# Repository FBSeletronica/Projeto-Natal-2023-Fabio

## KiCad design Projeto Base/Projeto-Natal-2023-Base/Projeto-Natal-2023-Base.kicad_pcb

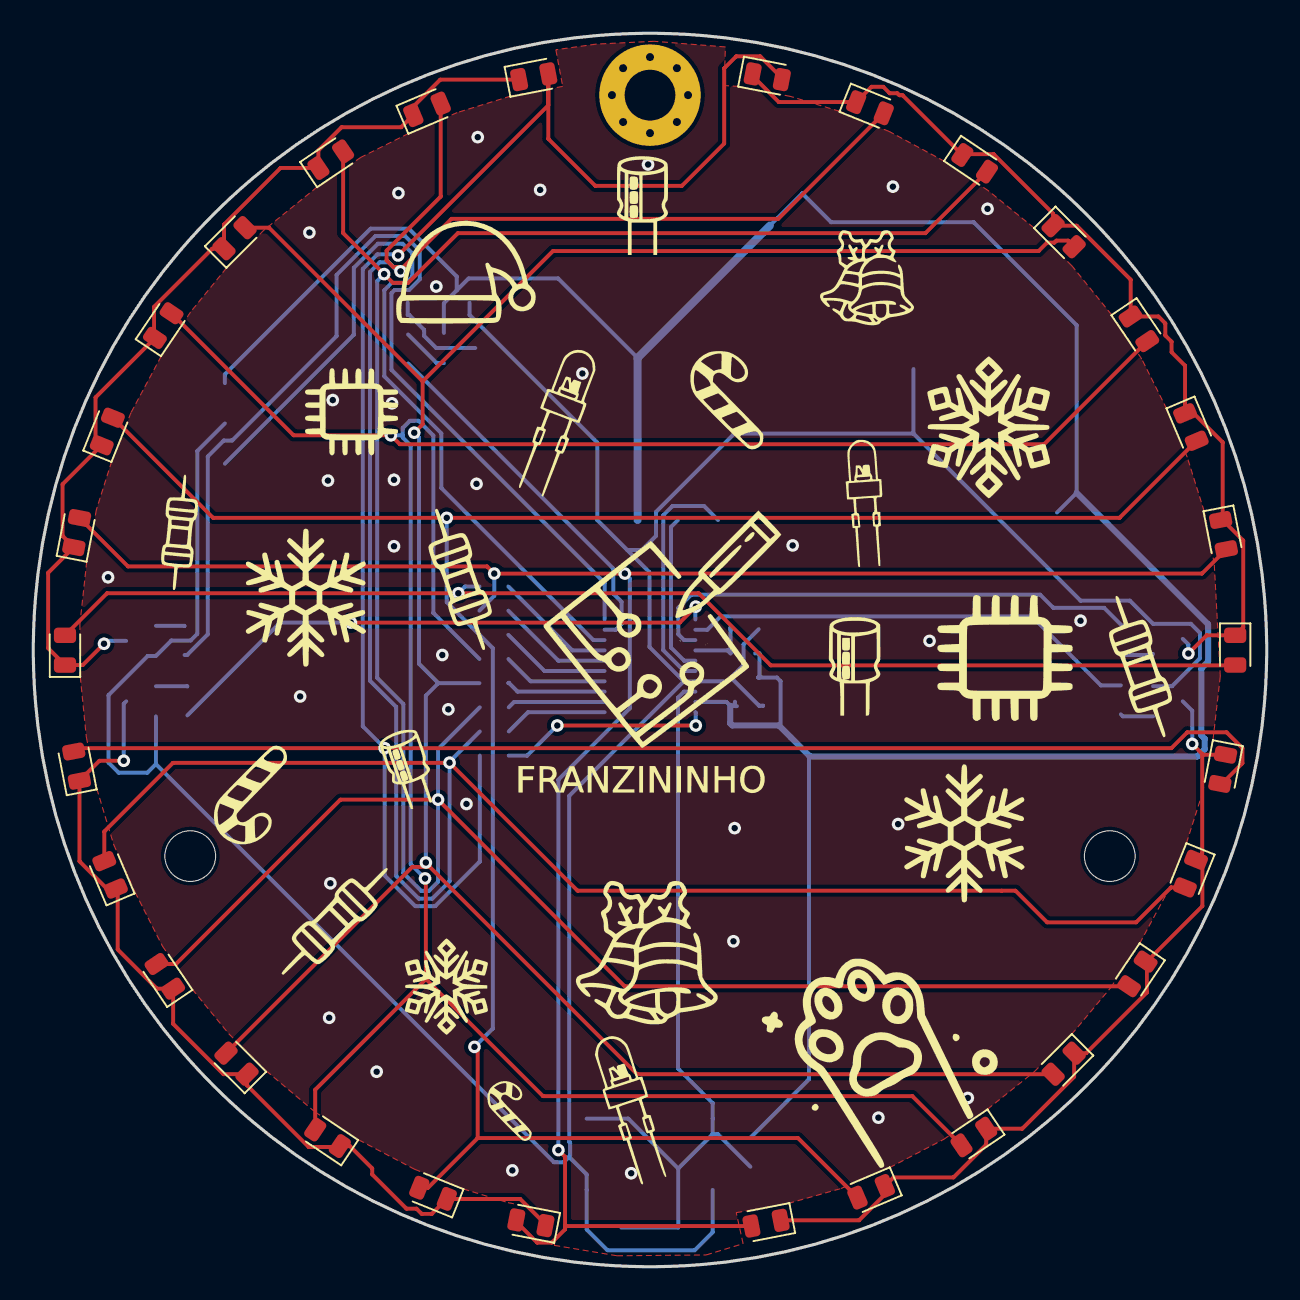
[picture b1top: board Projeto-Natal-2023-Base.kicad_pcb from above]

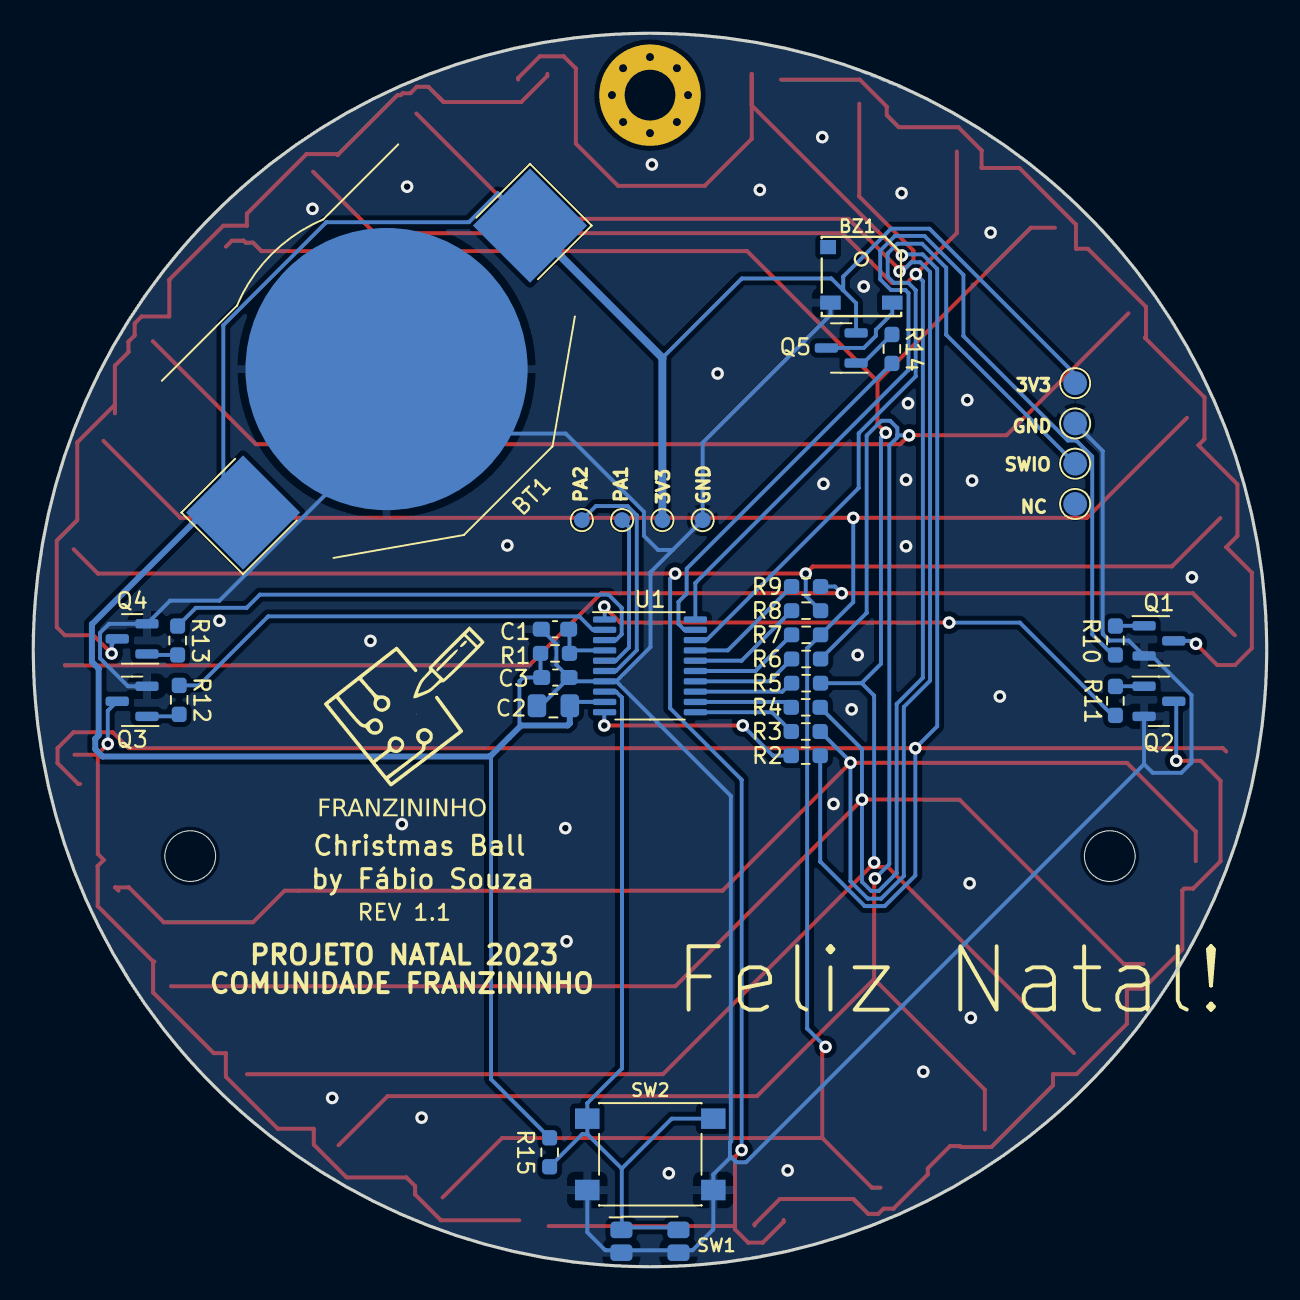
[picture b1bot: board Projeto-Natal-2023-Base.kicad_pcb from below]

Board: 2 copper layers, 77.8 x 77.8 mm, 68 parts (36 on the bottom side), 38 nets.

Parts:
BT1: BC-2001; BatteryHolder_Keystone_3002_1x2032
BZ1: MLT-5030; PassiveBuzzerSMD_JiangsuHuaneng_MLT-5030
C1, C3: 100nF; C_0603_1608Metric_Pad1.08x0.95mm_HandSolder
C2: 10uF; C_0805_2012Metric_Pad1.18x1.45mm_HandSolder
D1, D4, D7, D10, D13, D18, D21, D24, D27, D30: D-B080508B1-KS2; LED_0805_2012Metric
D2, D5, D8, D11, D14, D17, D20, D23, D26, D29: e17-21SURC/S530-A3/TR8; LED_0805_2012Metric
D3, D6, D9, D12, D15, D16, D19, D22, D25, D28: NCD0805G1; LED_0805_2012Metric
FURO1, FURO2: MountingHole_3.2mm_M3
J1, J2, J3, J4: Conn_01x01_Pin; TestPoint_Pad_D1.5mm
J5, J6, J7, J8: Conn_01x01_Pin; TestPoint_Pad_D1.0mm
Q1, Q2, Q3, Q4: BC817; SOT-23
Q5: MMBT3906; SOT-23
R1, R15: 10K; R_0603_1608Metric_Pad0.98x0.95mm_HandSolder
R2, R3, R4, R5, R6, R7, R8, R9, R10, R11, R12, R13, R14: 1K; R_0603_1608Metric_Pad0.98x0.95mm_HandSolder
SW1: EVQP7A; SW_SPST_EVQP7A
SW2: SW_Push; SW_Push_1P1T_NO_6x6mm_H9.5mm
U1: CH32V003F4P6; TSSOP-20_4.4x6.5mm_P0.65mm

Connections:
+3V3: BT1.1 (+), C2.1, C3.2, J2.1, J7.1, Q5.2 (E), R1.1, R15.2, U1.9 (VDD)
BT: R15.1, SW1.1, SW2.1, U1.8 (PD0)
BZR: R14.2, U1.19 (PD2)
C1: R10.1, U1.20 (PD3)
C2: R11.1, U1.1 (PD4)
C3: R12.1, U1.2 (PD5)
C4: R13.1, U1.3 (PD6)
GND: BT1.2 (-), BZ1.1 (-), C1.1, C2.2, C3.1, J3.1, J8.1, Q1.2 (E), Q2.2 (E), Q3.2 (E), Q4.2 (E), SW1.2, SW2.2, U1.7 (VSS)
L1: D1.2 (A), D9.2 (A), D22.2 (A), D30.2 (A), R2.2
L2: D2.2 (A), D10.2 (A), D21.2 (A), D29.2 (A), R3.2
L3: D3.2 (A), D11.2 (A), D20.2 (A), D28.2 (A), R4.2
L4: D4.2 (A), D12.2 (A), D19.2 (A), D27.2 (A), R5.2
L5: D5.2 (A), D13.2 (A), D18.2 (A), D26.2 (A), R6.2
L6: D6.2 (A), D14.2 (A), D17.2 (A), D25.2 (A), R7.2
L7: D7.2 (A), D15.2 (A), D16.2 (A), D24.2 (A), R8.2
L8: D8.2 (A), D23.2 (A), R9.2
unnamed: BZ1.2 (+), Q5.3 (C)
unnamed: D1.1 (K), D2.1 (K), D3.1 (K), D4.1 (K), D5.1 (K), D6.1 (K), D7.1 (K), D8.1 (K), Q1.3 (C)
unnamed: D9.1 (K), D10.1 (K), D11.1 (K), D12.1 (K), D13.1 (K), D14.1 (K), D15.1 (K), Q2.3 (C)
unnamed: D16.1 (K), D17.1 (K), D18.1 (K), D19.1 (K), D20.1 (K), D21.1 (K), D22.1 (K), Q3.3 (C)
unnamed: D23.1 (K), D24.1 (K), D25.1 (K), D26.1 (K), D27.1 (K), D28.1 (K), D29.1 (K), D30.1 (K), Q4.3 (C)
unnamed: Q1.1 (B), R10.2
unnamed: Q2.1 (B), R11.2
unnamed: Q3.1 (B), R12.2
unnamed: Q4.1 (B), R13.2
unnamed: Q5.1 (B), R14.1
unnamed: C1.2, R1.2, U1.4 (NRST/PD7)
unnamed: R2.1, U1.10 (PC0)
unnamed: R3.1, U1.11 (PC1)
unnamed: R4.1, U1.12 (PC2)
unnamed: R5.1, U1.13 (PC3)
unnamed: R6.1, U1.14 (PC4)
unnamed: R7.1, U1.15 (PC5)
unnamed: R8.1, U1.16 (PC6)
unnamed: R9.1, U1.17 (PC7)
PA1: J6.1, U1.5 (OSC_IN/PA1)
PA2: J5.1, U1.6 (OSC_OUT/PA2)
SWIO: J4.1, U1.18 (PD1)

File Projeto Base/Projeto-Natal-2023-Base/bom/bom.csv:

Designator,Footprint,Quantity,Value,LCSC Part #
BT1,BatteryHolder_Keystone_3002_1x2032,1,BC-2001,
BZ1,PassiveBuzzerSMD_JiangsuHuaneng_MLT-5030,1,MLT-5030,C95297
"C1, C3",0603,2,100nF,C14663
C2,0805,1,10uF,C15850
"D1, D10, D13, D18, D21, D24, D27, D30, D4, D7",0805,10,D-B080508B1-KS2,C108412
"D11, D14, D17, D2, D20, D23, D26, D29, D5, D8",0805,10,e17-21SURC/S530-A3/TR8,C72037
"D12, D15, D16, D19, D22, D25, D28, D3, D6, D9",0805,10,NCD0805G1,C84260
"Q1, Q2, Q3, Q4",SOT-23,4,BC817,C94412
Q5,SOT-23,1,MMBT3906,C111114
"R1, R15",0603,2,10K,C25804
"R10, R11, R12, R13, R14, R2, R3, R4, R5, R6, R7, R8, R9",0603,13,1K,C21190
SW1,SW_SPST_EVQP7A,1,EVQP7A,C79167
SW2,SW_Push_1P1T_NO_6x6mm_H9.5mm,1,SW_Push,C191626
U1,TSSOP-20_4.4x6.5mm_P0.65mm,1,CH32V003F4P6,

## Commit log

2023-11-15 Draft 1
2023-11-16 posicionando os componentes
2023-11-17 routing...
2023-11-19 v1.0.0
2023-11-20 update 3D
2023-11-20 Versão para revisão
2023-11-20 update silk
2023-11-21 Adicionando pinos extras e resistor de pullup para o BT
2023-11-21 Fim v1.0.0
2023-11-22 V1.1.0
    Placa com 78,8 mm de diametro
2023-11-22 update files
2023-11-22 Versao fabricada
2023-11-22 update files
    Nenhuma alteração no layout
2023-11-22 adicionando git ignore
2023-11-23 adicionando + info para fabricação
    BOM, iBOM, custos atẽ o momento, dimensões
2023-11-23 adicionando imagem e planilha para posicionamento dos leds
2023-11-23 Adicionando alguns datasheets usados
2023-11-23 Organizando arquivos em pastas
2023-11-26 atualizando custos
